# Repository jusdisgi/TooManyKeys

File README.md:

# Too Many Keys
Soon to be renamed*

This is a 54-key, ergonomic split keyboard with a few tricks. Some of the features include:
- 1.69in color [LCD screen](https://www.waveshare.com/product/displays/lcd-oled/lcd-oled-3/1.69inch-lcd-module.htm)
- Per-key LEDs, using [WS2812B-2020](https://www.adafruit.com/product/4684)
- A roller encoder based on [CKW12](https://github.com/kumamuk-git/CKW12/tree/main) by Kumamuk, but integrated into the main PCB
- Kailh [PG1316S](https://holykeebs.com/products/kailh-pg1316s-butterfly-switch-10-pack) ultra-low profile switches
- A totally absurd [battery](https://www.digikey.com/en/products/detail/maker-emporium-ltd/PIS-1131/13283430) to run all of this stuff...5Ahr!!

## Schematics and Ergogen, just like PB and Chocolate!
If that seems absurd to you, you need to read [my new doc](https://github.com/jusdisgi/TooManyKeys/blob/main/Schematics_and_Ergogen.md)

## Work in Progress

I think it might be done? Could it be?
Please take a look and let me know if you see anything wrong!

## Where is everything?
[Left Half PCB](https://github.com/jusdisgi/TooManyKeys/blob/main/toomanykeys_left.kicad_pcb)
[Right Half PCB](https://github.com/jusdisgi/TooManyKeys/blob/main/toomanykeys_right.kicad_pcb)

[Left Half Schematic](https://github.com/jusdisgi/TooManyKeys/blob/main/toomanykeys_left.kicad_sch)
[Right Half Schematic](https://github.com/jusdisgi/TooManyKeys/blob/main/toomanykeys_right.kicad_sch)

[Ergogen Config](https://github.com/jusdisgi/TooManyKeys/blob/main/config.yaml)

## Some pics of the design

*the name has been chosen by the intended end-user, but will not be applied to the board until it actually exists in the real world.

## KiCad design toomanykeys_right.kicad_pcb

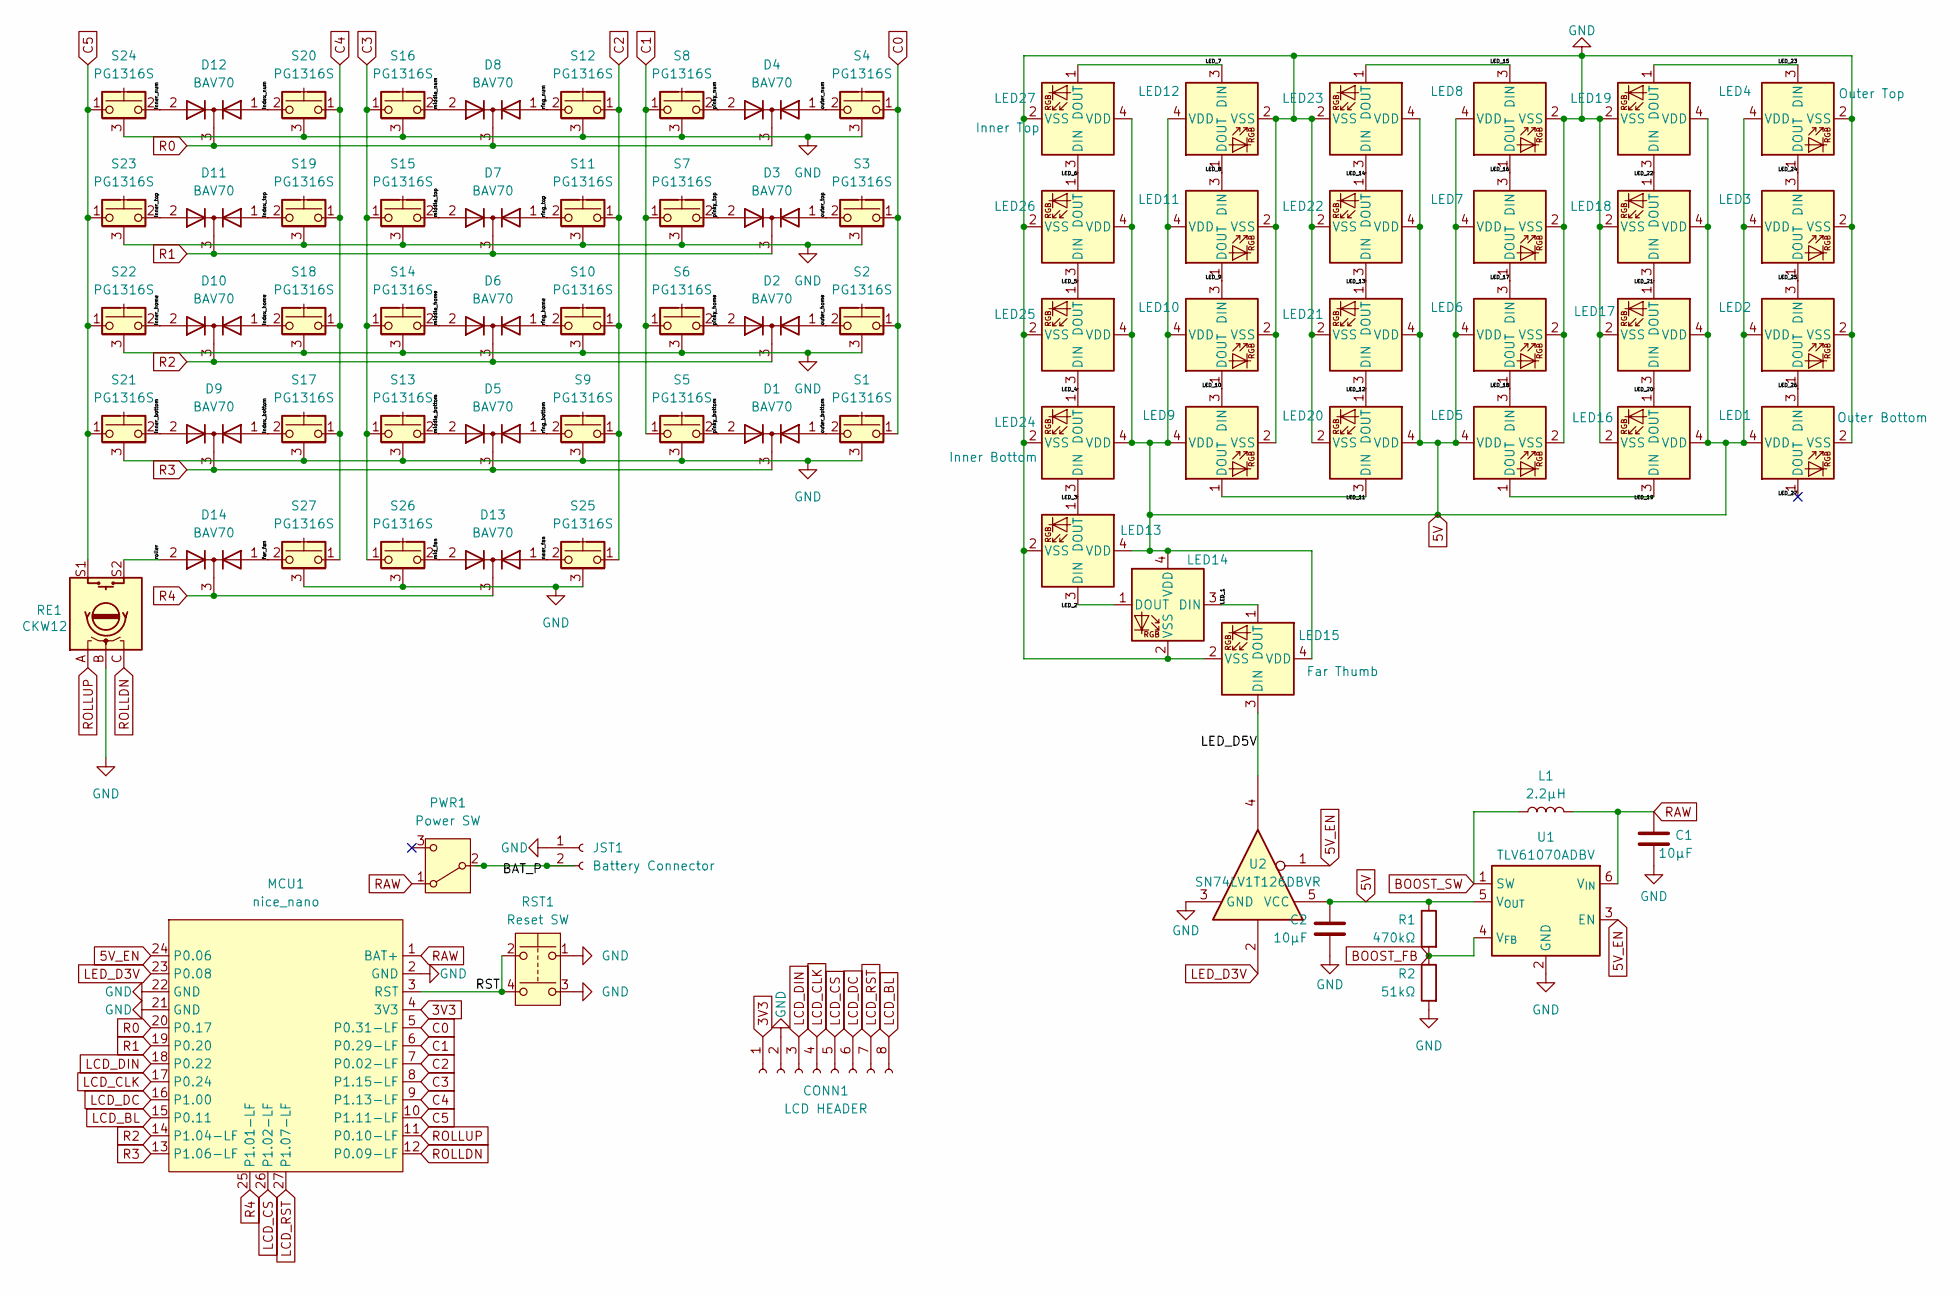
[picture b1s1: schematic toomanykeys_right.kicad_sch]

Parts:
C1, C2: 10μF; C_0603_1608Metric
CONN1: LCD HEADER; Molex_PicoBlade_53261-0871_1x08-1MP_P1.25mm_Horizontal
D1, D2, D3, D4, D5, D6, D7, D8, D9, D10, D11, D12, D13, D14: BAV70; BAV70 SOT23
JST1: Battery Connector; battery_connector_jst_ph_2
L1: 2.2μH; L_CJIANG_FTC404030S_4.1x4.1x3.0_SMD
LED1: Outer Bottom; LED_WS2812B-2020_PLCC4_2.0x2.0mm
LED2, LED3, LED5, LED6, LED7, LED8, LED9, LED10, LED11, LED12, LED13, LED14, LED16, LED17, LED18, LED19, LED20, LED21, LED22, LED23, LED25, LED26: WS2812B-2020; LED_WS2812B-2020_PLCC4_2.0x2.0mm
LED4: Outer Top; LED_WS2812B-2020_PLCC4_2.0x2.0mm
LED15: Far Thumb; LED_WS2812B-2020_PLCC4_2.0x2.0mm
LED24: Inner Bottom; LED_WS2812B-2020_PLCC4_2.0x2.0mm
LED27: Inner Top; LED_WS2812B-2020_PLCC4_2.0x2.0mm
MCU1: nice_nano; mcu_nice_nano
PWR1: Power SW; power_switch_smd_side
R1: 470kΩ; R_0603_1608Metric
R2: 51kΩ; R_0603_1608Metric
RE1: CKW12
RST1: Reset SW; reset_switch_smd_side
S1, S2, S3, S4, S5, S6, S7, S8, S9, S10, S11, S12, S13, S14, S15, S16, S17, S18, S19, S20, S21, S22, S23, S24, S25, S26, S27: PG1316S
U1: TLV61070ADBV; SOT-23-6
U2: SN74LV1T126DBVR; SOT-23-5

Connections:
3V3: CONN1.1, MCU1.4 (3V3)
5V: C2.1, LED1.4 (VDD), LED2.4 (VDD), LED3.4 (VDD), LED4.4 (VDD), LED5.4 (VDD), LED6.4 (VDD), LED7.4 (VDD), LED8.4 (VDD), LED9.4 (VDD), LED10.4 (VDD), LED11.4 (VDD), LED12.4 (VDD), LED13.4 (VDD), LED14.4 (VDD), LED15.4 (VDD), LED16.4 (VDD), LED17.4 (VDD), LED18.4 (VDD), LED19.4 (VDD), LED20.4 (VDD), LED21.4 (VDD), LED22.4 (VDD), LED23.4 (VDD), LED24.4 (VDD), LED25.4 (VDD), LED26.4 (VDD), LED27.4 (VDD), R1.1, U1.5 (V_{OUT}), U2.5 (VCC)
5V_EN: MCU1.24 (P0.06), U1.3 (EN), U2.1
/BAT_P: JST1.2, PWR1.2 (B)
/LED_1: LED14.3 (DIN), LED15.1 (DOUT)
/LED_2: LED13.3 (DIN), LED14.1 (DOUT)
/LED_3: LED13.1 (DOUT), LED24.3 (DIN)
/LED_4: LED24.1 (DOUT), LED25.3 (DIN)
/LED_5: LED25.1 (DOUT), LED26.3 (DIN)
/LED_6: LED26.1 (DOUT), LED27.3 (DIN)
/LED_7: LED12.3 (DIN), LED27.1 (DOUT)
/LED_8: LED11.3 (DIN), LED12.1 (DOUT)
/LED_9: LED10.3 (DIN), LED11.1 (DOUT)
/LED_10: LED9.3 (DIN), LED10.1 (DOUT)
/LED_11: LED9.1 (DOUT), LED20.3 (DIN)
/LED_12: LED20.1 (DOUT), LED21.3 (DIN)
/LED_13: LED21.1 (DOUT), LED22.3 (DIN)
/LED_14: LED22.1 (DOUT), LED23.3 (DIN)
/LED_15: LED8.3 (DIN), LED23.1 (DOUT)
/LED_16: LED7.3 (DIN), LED8.1 (DOUT)
/LED_17: LED6.3 (DIN), LED7.1 (DOUT)
/LED_18: LED5.3 (DIN), LED6.1 (DOUT)
/LED_19: LED5.1 (DOUT), LED16.3 (DIN)
/LED_20: LED16.1 (DOUT), LED17.3 (DIN)
/LED_21: LED17.1 (DOUT), LED18.3 (DIN)
/LED_22: LED18.1 (DOUT), LED19.3 (DIN)
/LED_23: LED4.3 (DIN), LED19.1 (DOUT)
/LED_24: LED3.3 (DIN), LED4.1 (DOUT)
/LED_25: LED2.3 (DIN), LED3.1 (DOUT)
/LED_26: LED1.3 (DIN), LED2.1 (DOUT)
/LED_27: LED1.1 (DOUT)
/LED_D5V: LED15.3 (DIN), U2.4
/RST: MCU1.3 (RST), RST1.2, RST1.4
/far_fan: D14.1 (A), S27.2
/index_bottom: D9.1 (A), S17.2
/index_home: D10.1 (A), S18.2
/index_num: D12.1 (A), S20.2
/index_top: D11.1 (A), S19.2
/inner_bottom: D9.2 (A), S21.2
/inner_home: D10.2 (A), S22.2
/inner_num: D12.2 (A), S24.2
/inner_top: D11.2 (A), S23.2
/mid_fan: D13.2 (A), S26.2
/middle_bottom: D5.2 (A), S13.2
/middle_home: D6.2 (A), S14.2
/middle_num: D8.2 (A), S16.2
/middle_top: D7.2 (A), S15.2
/near_fan: D13.1 (A), S25.2
/outer_bottom: D1.1 (A), S1.2
/outer_home: D2.1 (A), S2.2
/outer_num: D4.1 (A), S4.2
/outer_top: D3.1 (A), S3.2
/pinky_bottom: D1.2 (A), S5.2
/pinky_home: D2.2 (A), S6.2
/pinky_num: D4.2 (A), S8.2
/pinky_top: D3.2 (A), S7.2
/ring_bottom: D5.1 (A), S9.2
/ring_home: D6.1 (A), S10.2
/ring_num: D8.1 (A), S12.2
/ring_top: D7.1 (A), S11.2
/roller: D14.2 (A), RE1.S2
BOOST_FB: R1.2, R2.1, U1.4 (V_{FB})
BOOST_SW: L1.2, U1.1 (SW)
C0: MCU1.5 (P0.31-LF), S1.1, S2.1, S3.1, S4.1
C1: MCU1.6 (P0.29-LF), S5.1, S6.1, S7.1, S8.1
C2: MCU1.7 (P0.02-LF), S9.1, S10.1, S11.1, S12.1, S25.1
C3: MCU1.8 (P1.15-LF), S13.1, S14.1, S15.1, S16.1, S26.1
C4: MCU1.9 (P1.13-LF), S17.1, S18.1, S19.1, S20.1, S27.1
C5: MCU1.10 (P1.11-LF), RE1.S1, S21.1, S22.1, S23.1, S24.1
GND: C1.2, C2.2, CONN1.2, JST1.1, LED1.2 (VSS), LED2.2 (VSS), LED3.2 (VSS), LED4.2 (VSS), LED5.2 (VSS), LED6.2 (VSS), LED7.2 (VSS), LED8.2 (VSS), LED9.2 (VSS), LED10.2 (VSS), LED11.2 (VSS), LED12.2 (VSS), LED13.2 (VSS), LED14.2 (VSS), LED15.2 (VSS), LED16.2 (VSS), LED17.2 (VSS), LED18.2 (VSS), LED19.2 (VSS), LED20.2 (VSS), LED21.2 (VSS), LED22.2 (VSS), LED23.2 (VSS), LED24.2 (VSS), LED25.2 (VSS), LED26.2 (VSS), LED27.2 (VSS), MCU1.2 (GND), MCU1.21 (GND), MCU1.22 (GND), R2.2, RE1.B, RST1.1, RST1.3, S1.3 (B), S2.3 (B), S3.3 (B), S4.3 (B), S5.3 (B), S6.3 (B), S7.3 (B), S8.3 (B), S9.3 (B), S10.3 (B), S11.3 (B), S12.3 (B), S13.3 (B), S14.3 (B), S15.3 (B), S16.3 (B), S17.3 (B), S18.3 (B), S19.3 (B), S20.3 (B), S21.3 (B), S22.3 (B), S23.3 (B), S24.3 (B), S25.3 (B), S26.3 (B), S27.3 (B), U1.2 (GND), U2.3 (GND)
LCD_BL: CONN1.8, MCU1.15 (P0.11)
LCD_CLK: CONN1.4, MCU1.17 (P0.24)
LCD_CS: CONN1.5, MCU1.26 (P1.02-LF)
LCD_DC: CONN1.6, MCU1.16 (P1.00)
LCD_DIN: CONN1.3, MCU1.18 (P0.22)
LCD_RST: CONN1.7, MCU1.27 (P1.07-LF)
LED_D3V: MCU1.23 (P0.08), U2.2
R0: D4.3 (K), D8.3 (K), D12.3 (K), MCU1.20 (P0.17)
R1: D3.3 (K), D7.3 (K), D11.3 (K), MCU1.19 (P0.20)
R2: D2.3 (K), D6.3 (K), D10.3 (K), MCU1.14 (P1.04-LF)
R3: D1.3 (K), D5.3 (K), D9.3 (K), MCU1.13 (P1.06-LF)
R4: D13.3 (K), D14.3 (K), MCU1.25 (P1.01-LF)
RAW: C1.1, L1.1, MCU1.1 (BAT+), PWR1.1 (A), U1.6 (V_{IN})
ROLLDN: MCU1.12 (P0.09-LF), RE1.C
ROLLUP: MCU1.11 (P0.10-LF), RE1.A

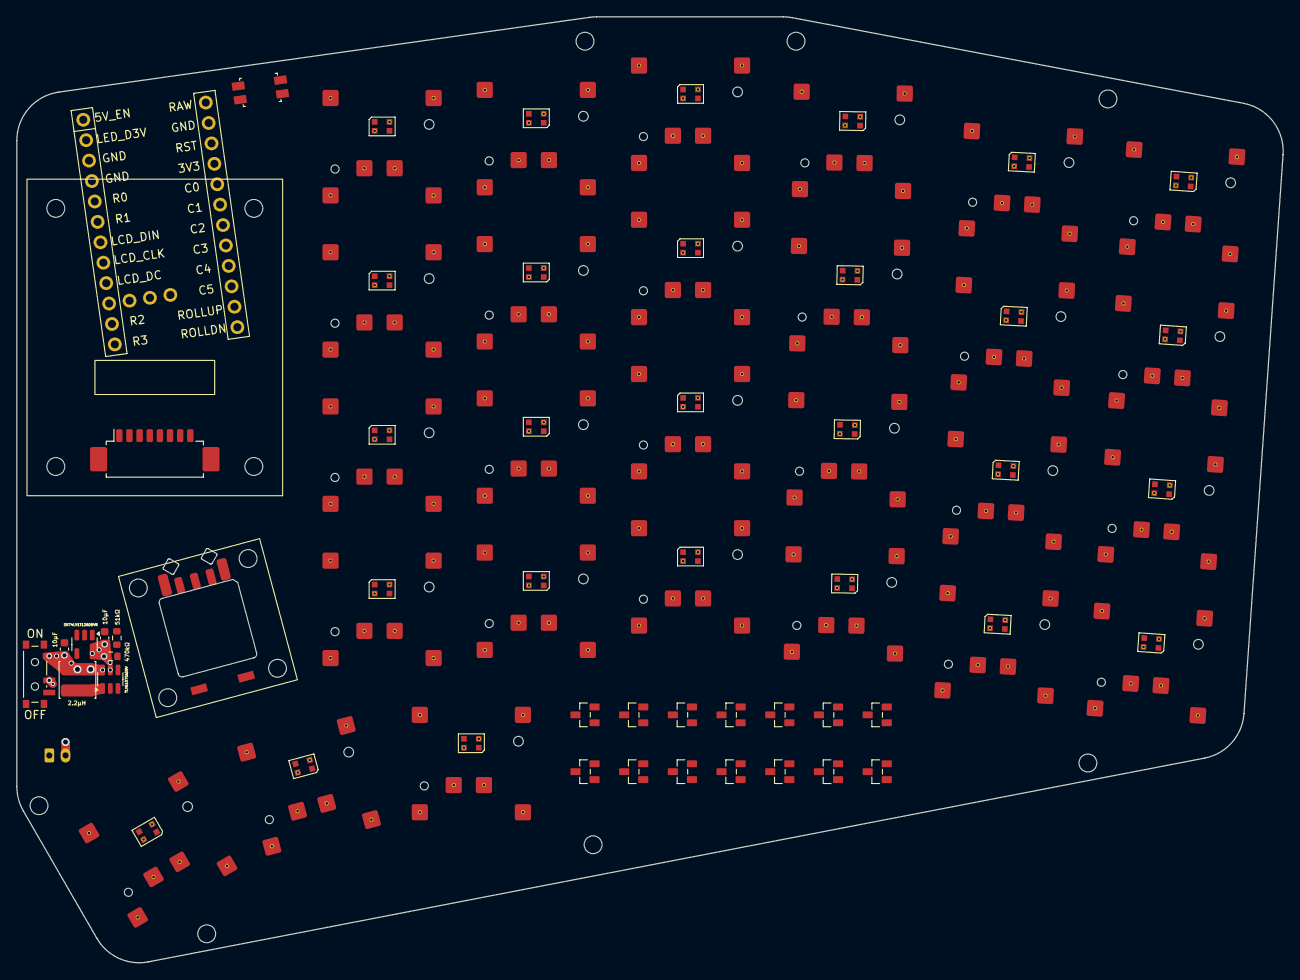
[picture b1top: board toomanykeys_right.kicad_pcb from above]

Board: 6 copper layers, 156.0 x 116.5 mm, 89 parts (1 on the bottom side), 84 nets.

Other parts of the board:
LCD1: LCD_1.69_Waveshare
MH1, MH2, MH3, MH4, MH5, MH6, MH7: mounting_hole_npth

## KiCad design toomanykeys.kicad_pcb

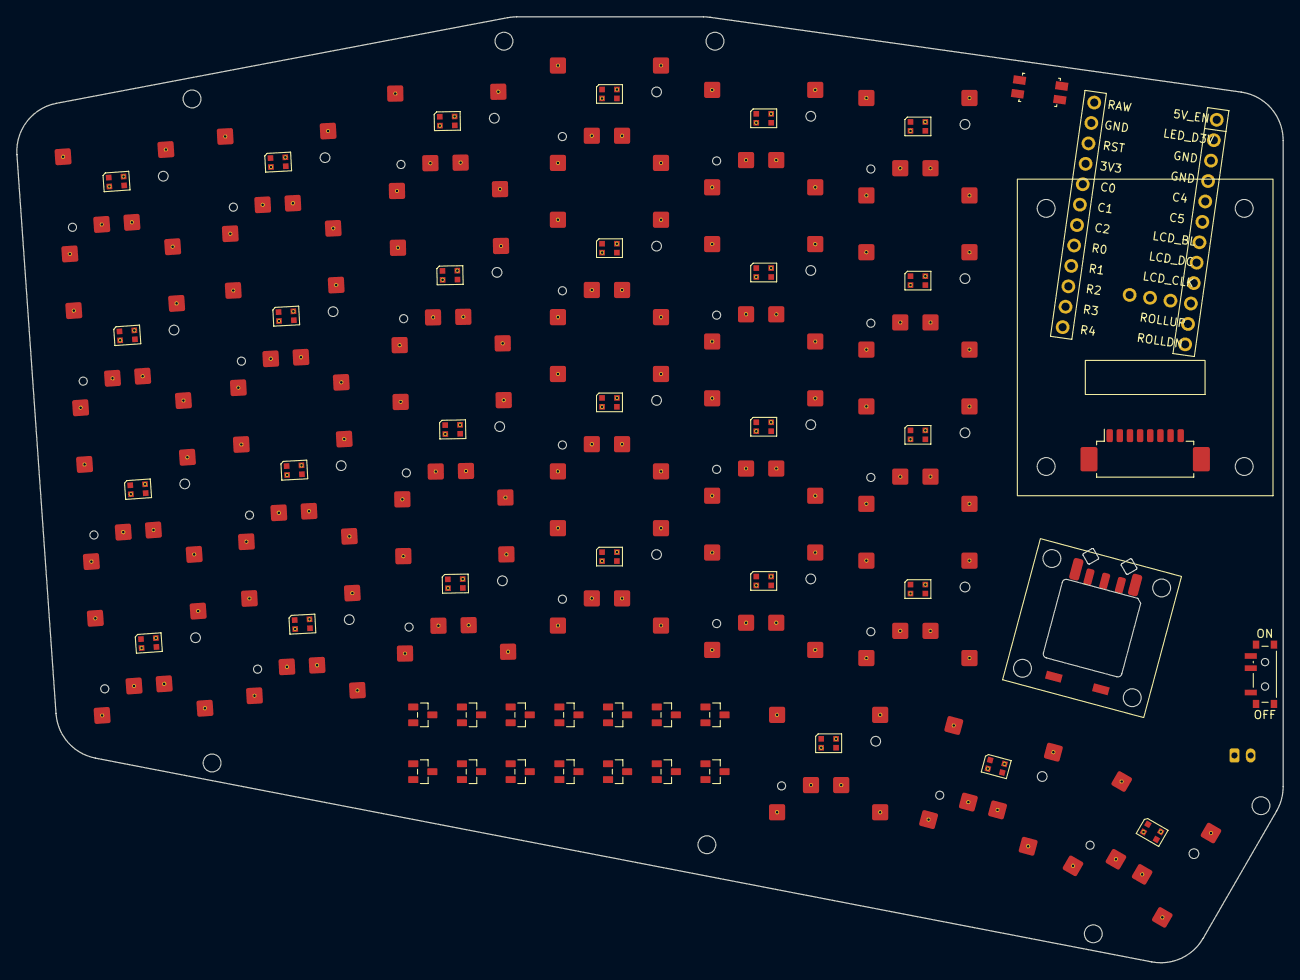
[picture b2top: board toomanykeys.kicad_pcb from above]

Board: 2 copper layers, 156.0 x 116.5 mm, 82 parts (1 on the bottom side), 79 nets, no tracks yet.

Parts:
CONN1: Molex_PicoBlade_53261-0871_1x08-1MP_P1.25mm_Horizontal
D1, D2, D3, D4, D5, D6, D7, D8, D9, D10, D11, D12, D13, D14: BAV70; BAV70 SOT23
JST1: battery_connector_jst_ph_2
LCD1: LCD_1.69_Waveshare
LED1, LED2, LED3, LED4, LED5, LED6, LED7, LED8, LED9, LED10, LED11, LED12, LED13, LED14, LED15, LED16, LED17, LED18, LED19, LED20, LED21, LED22, LED23, LED24, LED25, LED26, LED27: LED_WS2812B-2020_PLCC4_2.0x2.0mm
MCU1: mcu_nice_nano
MH1, MH2, MH3, MH4, MH5, MH6, MH7: mounting_hole_npth
PWR1: power_switch_smd_side
RE1: CKW12
RST1: reset_switch_smd_side
S1, S2, S3, S4, S5, S6, S7, S8, S9, S10, S11, S12, S13, S14, S15, S16, S17, S18, S19, S20, S21, S22, S23, S24, S25, S26, S27: PG1316S

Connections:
3V3: CONN1.1, MCU1.21
5V: LED1.2, LED2.2, LED3.2, LED4.2, LED5.2, LED6.2, LED7.2, LED8.2, LED9.2, LED10.2, LED11.2, LED12.2, LED13.2, LED14.2, LED15.2, LED16.2, LED17.2, LED18.2, LED19.2, LED20.2, LED21.2, LED22.2, LED23.2, LED24.2, LED25.2, LED26.2, LED27.2
BAT_P: JST1.2, PWR1.2
C0: MCU1.20, S1.1, S2.1, S3.1, S4.1
C1: MCU1.19, S5.1, S6.1, S7.1, S8.1
C2: MCU1.18, S9.1, S10.1, S11.1, S12.1, S25.1
C3: MCU1.27, S13.1, S14.1, S15.1, S16.1, S26.1
C4: MCU1.5, S17.1, S18.1, S19.1, S20.1, S27.1
C5: MCU1.6, RE1.S1, S21.1, S22.1, S23.1, S24.1
GND: CONN1.2, JST1.1, LED1.4, LED2.4, LED3.4, LED4.4, LED5.4, LED6.4, LED7.4, LED8.4, LED9.4, LED10.4, LED11.4, LED12.4, LED13.4, LED14.4, LED15.4, LED16.4, LED17.4, LED18.4, LED19.4, LED20.4, LED21.4, LED22.4, LED23.4, LED24.4, LED25.4, LED26.4, LED27.4, MCU1.3, MCU1.4, MCU1.23, RE1.B, RST1.1, RST1.3, S1.3, S2.3, S3.3, S4.3, S5.3, S6.3, S7.3, S8.3, S9.3, S10.3, S11.3, S12.3, S13.3, S14.3, S15.3, S16.3, S17.3, S18.3, S19.3, S20.3, S21.3, S22.3, S23.3, S24.3, S25.3, S26.3, S27.3
LCD_BL: CONN1.8, MCU1.7
LCD_CLK: CONN1.4, MCU1.9
LCD_CS: CONN1.5, MCU1.26
LCD_DC: CONN1.6, MCU1.8
LCD_DIN: CONN1.3, MCU1.10
LCD_RST: CONN1.7, MCU1.25
LED_1: LED26.1, LED27.3
LED_2: LED25.1, LED26.3
LED_3: LED21.1, LED25.3
LED_4: LED21.3, LED22.1
LED_5: LED22.3, LED23.1
LED_6: LED23.3, LED24.1
LED_7: LED20.1, LED24.3
LED_8: LED19.1, LED20.3
LED_9: LED18.1, LED19.3
LED_10: LED17.1, LED18.3
LED_11: LED13.1, LED17.3
LED_12: LED13.3, LED14.1
LED_13: LED14.3, LED15.1
LED_14: LED15.3, LED16.1
LED_15: LED12.1, LED16.3
LED_16: LED11.1, LED12.3
LED_17: LED10.1, LED11.3
LED_18: LED9.1, LED10.3
LED_19: LED5.1, LED9.3
LED_20: LED5.3, LED6.1
LED_21: LED6.3, LED7.1
LED_22: LED7.3, LED8.1
LED_23: LED4.1, LED8.3
LED_24: LED3.1, LED4.3
LED_25: LED2.1, LED3.3
LED_26: LED1.1, LED2.3
R0: D1.3, D2.3, D3.3, MCU1.17
R1: D4.3, D5.3, D6.3, MCU1.16
R2: D7.3, D8.3, D9.3, MCU1.15
R3: D10.3, D11.3, D12.3, MCU1.14
R4: D13.3, D14.3, MCU1.13
RAW: MCU1.24, PWR1.3
ROLLDN: MCU1.12, RE1.C
ROLLUP: MCU1.11, RE1.A
RST: MCU1.22, RST1.2, RST1.4
finger_index_bottom: D12.1, S17.2
finger_index_home: D9.1, S18.2
finger_index_num: D3.1, S20.2
finger_index_top: D6.1, S19.2
finger_inner_bottom: D12.2, S21.2
finger_inner_home: D9.2, S22.2
finger_inner_num: D3.2, S24.2
finger_inner_top: D6.2, S23.2
finger_middle_bottom: D11.1, S13.2
finger_middle_home: D8.2, S14.2
finger_middle_num: D2.2, S16.2
finger_middle_top: D5.2, S15.2
finger_outer_bottom: D10.2, S1.2
finger_outer_home: D7.1, S2.2
finger_outer_num: D1.1, S4.2
finger_outer_top: D4.1, S3.2
finger_pinky_bottom: D10.1, S5.2
finger_pinky_home: D7.2, S6.2
finger_pinky_num: D1.2, S8.2
finger_pinky_top: D4.2, S7.2
finger_ring_bottom: D11.2, S9.2
finger_ring_home: D8.1, S10.2
finger_ring_num: D2.1, S12.2
finger_ring_top: D5.1, S11.2
roller: D13.1, RE1.S2
thumb_far_fan: D14.2, S27.2
thumb_mid_fan: D14.1, S26.2
thumb_near_fan: D13.2, S25.2

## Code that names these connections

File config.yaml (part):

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    bav70_bottom1: &bav70proto #Ref: D1
      key:
        A1: outer_bottom
        A2: pinky_bottom
        C: R3
      anchor: &bav70anchor
        - ref: finger_middle_bottom
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    bav70_home1: #Ref: D2
      <<:  *bav70proto
      key.A1: outer_home
      key.A2: pinky_home
      key.C: R2
      anchor:
        <<: *bav70anchor
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    bav70_top1: #Ref: D3
      <<:  *bav70proto
      key.A1: outer_top
      key.A2: pinky_top
      key.C: R1
      anchor:
        <<: *bav70anchor
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    bav70_num1: #Ref: D4
      <<:  *bav70proto
      key.A1: outer_num
      key.A2: pinky_num
      key.C: R0
      anchor:
        <<: *bav70anchor
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          shift: [10, 12]
    screw_pcb_left_bottom:
      anchor:
        - ref: finger_pinky_bottom
          shift: [-12,-14]
    screw_pcb_left_mid_top:
      anchor:
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
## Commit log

2025-05-30 Initial commit.
2025-05-30 Create LICENSE
2025-05-31 Add BAV70 field and rotary, work on outlines.
2025-06-02 Add CKW12 Roller Encoder Footprint.
2025-06-02 Add comments to CKW12 Footprint.
2025-06-04 Add nets to MCU, fix diode assignments, work on LEDs.
2025-06-05 Complete draft 3 of routing, near complete. Fix pad positions on roller encoder.
2025-06-05 Add LCD outline to board, move other components as needed. Add 3D model support to several footprints, add model for CKW12 roller encoder.
2025-06-05 Work on power routing/design. Current thinking in main PCB file.
2025-06-05 Add schematic.
2025-06-05 Fix whatever boneheaded thing I did to mess up all the boostier pads.
2025-06-05 Add gitignore to cull backups and cruft.
2025-06-06 Complete routing draft.
2025-06-06 Finish schematic. Partial routing draft. Minor changes to via sizes in ergogen.
2025-06-06 Redo schematic references to match ergogen, work on connecting sch and pcb.
2025-06-06 Integrate schematic with PCB
2025-06-07 Finish clean routing. Attempted sync of schematic failed, but board LGTM and passes DRC other than CKW12 edge issues of no concern.
2025-06-07 wtfO
2025-06-07 Successfully sync schematic and PCB for left halfgit add .git add .git add .!
2025-06-08 Create right half schematic, successfully sync with new right half PCB!
2025-06-08 Fully route left half. Schematic and PCB both clean!
2025-06-08 Fix overzealous gitignore.
2025-06-08 Minor cleanup on left side. Add a few vias to connect islands, move a few traces.
2025-06-08 Route right half. Make minor improvements on left. Ready for production?
2025-06-09 Clean up.
2025-06-09 Improve schematic readability by removing some wires and adding some GND and 5V labels.
2025-06-14 Cleanup.
2025-06-20 Cleanup
